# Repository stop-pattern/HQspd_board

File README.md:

# HQspd_board
はんきうの速度計ドライブ基板のつもりがおもちゃ基板が出来ちゃったやつ
今後どうするかは謎

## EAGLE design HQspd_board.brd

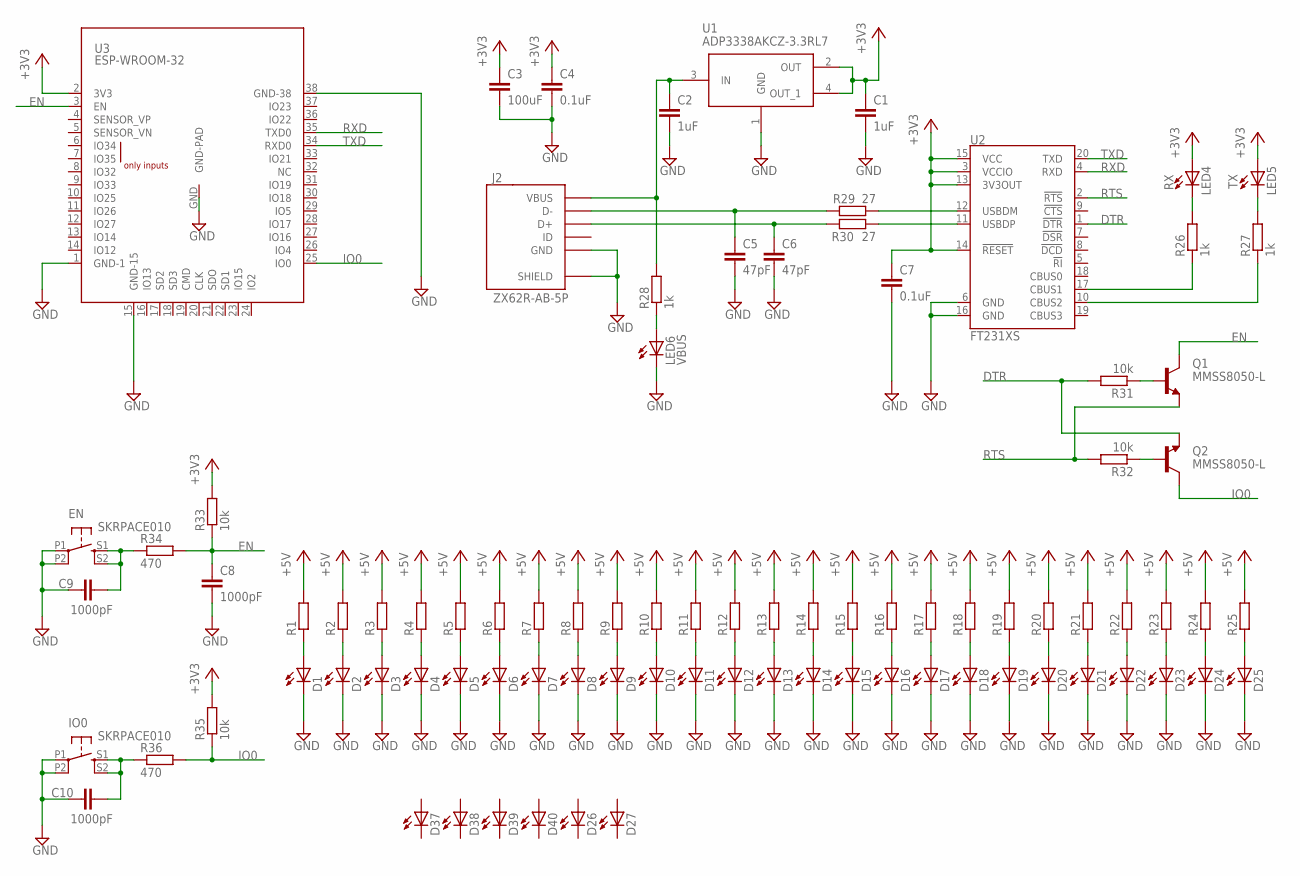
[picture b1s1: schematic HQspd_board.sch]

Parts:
C1, C2: 1uF; C0603
C3: 100uF; C1210
C4, C7: 0.1uF; C0603
C5, C6: 47pF; C0603
C8, C9, C10: 1000pF; C0603
D1, D2, D3, D4, D5, D6, D7, D8, D9, D10, D11, D12, D13, D14, D15, D16, D17, D18, D19, D20, D21, D22, D23, D24, D25: LEDCHIPLED_0603; CHIPLED_0603
D26, D27, D37, D38, D39, D40: LED3MM
EN: SKRPACE010
IO0: SKRPACE010
J2: ZX62R-AB-5P; ZX62R-B-5PA
LED4: RX; CHIPLED_0603
LED5: TX; CHIPLED_0603
LED6: VBUS; CHIPLED_0603
Q1, Q2: MMSS8050-L; SOT23
R1, R2, R3, R4, R5, R6, R7, R8, R9, R10, R11, R12, R13, R14, R15, R16, R17, R18, R19, R20, R21, R22, R23, R24, R25: R-EU_R0603; R0603
R26, R27, R28: 1k; R0603
R29, R30: 27; R0603
R31, R32, R33, R35: 10k; R0603
R34, R36: 470; R0603
U1: ADP3338AKCZ-3.3RL7; SOT230P700X180-4N
U2: FT231XS; SSOP20_L
U3: ESP-WROOM-32

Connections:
+3V3: C1.1, C3.1, C4.1, C7.1, LED4.A, LED5.A, R33.2, R35.2, U1.2 (OUT), U1.4 (OUT_1), U2.3 (VCCIO), U2.13 (3V3OUT), U2.14 (!RESET), U2.15 (VCC), U3.2 (3V3)
+5V: R1.2, R2.2, R3.2, R4.2, R5.2, R6.2, R7.2, R8.2, R9.2, R10.2, R11.2, R12.2, R13.2, R14.2, R15.2, R16.2, R17.2, R18.2, R19.2, R20.2, R21.2, R22.2, R23.2, R24.2, R25.2
+5V1: C2.1, J2.VCC (VBUS), R28.2, U1.3 (IN)
D2_N1: R29.2, U2.12 (USBDM)
D2_P1: R30.2, U2.11 (USBDP)
DTR: Q2.E, R31.2, U2.1 (!DTR)
D_N1: C5.1, J2.D-, R29.1
D_P1: C6.1, J2.D+, R30.1
EN: C8.1, Q1.C, R33.1, R34.2, U3.3 (EN)
GND: C1.2, C2.2, C3.2, C4.2, C5.2, C6.2, C7.2, C8.2, C9.1, C10.1, D1.C, D2.C, D3.C, D4.C, D5.C, D6.C, D7.C, D8.C, D9.C, D10.C, D11.C, D12.C, D13.C, D14.C, D15.C, D16.C, D17.C, D18.C, D19.C, D20.C, D21.C, D22.C, D23.C, D24.C, D25.C, EN.P1, EN.P2 (P1), IO0.P1, IO0.P2 (P1), J2.GND, J2.SHIELD@1 (SHIELD), J2.SHIELD@2 (SHIELD), J2.SHIELD@3 (SHIELD), J2.SHIELD@4 (SHIELD), LED6.C, U1.1 (GND), U2.6 (GND), U2.16 (GND), U3.1 (GND-1), U3.15 (GND-15), U3.38 (GND-38), U3.GND (GND-PAD)
IO0: Q2.C, R35.1, R36.2, U3.25 (IO0)
unnamed: D1.A, R1.1
unnamed: D11.A, R11.1
unnamed: D2.A, R2.1
unnamed: D3.A, R3.1
unnamed: D4.A, R4.1
unnamed: D5.A, R5.1
unnamed: D6.A, R6.1
unnamed: D7.A, R7.1
unnamed: D8.A, R8.1
unnamed: D9.A, R9.1
unnamed: D10.A, R10.1
unnamed: D12.A, R12.1
unnamed: D13.A, R13.1
unnamed: D14.A, R14.1
unnamed: D15.A, R15.1
unnamed: D16.A, R16.1
unnamed: D17.A, R17.1
unnamed: D18.A, R18.1
unnamed: D19.A, R19.1
unnamed: D20.A, R20.1
unnamed: D21.A, R21.1
unnamed: D22.A, R22.1
unnamed: D23.A, R23.1
unnamed: D24.A, R24.1
unnamed: D25.A, R25.1
unnamed: LED4.C, R26.2
unnamed: LED5.C, R27.2
unnamed: C9.2, EN.S1 (S), EN.S2 (S1), R34.1
unnamed: C10.2, IO0.S1 (S), IO0.S2 (S1), R36.1
unnamed: R26.1, U2.17 (CBUS1)
unnamed: R27.1, U2.10 (CBUS2)
unnamed: LED6.A, R28.1
unnamed: Q1.B, R31.1
unnamed: Q2.B, R32.1
RTS: Q1.E, R32.2, U2.2 (!RTS)
RXD: U2.4 (RXD), U3.35 (TXD0)
TXD: U2.20 (TXD), U3.34 (RXD0)

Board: 2 copper layers, 88 parts (50 on the bottom side), 48 nets, no tracks yet.

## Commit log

2020-10-25 [add] 基板
    ひと段落着いたやつ
2020-10-25 [add] image
